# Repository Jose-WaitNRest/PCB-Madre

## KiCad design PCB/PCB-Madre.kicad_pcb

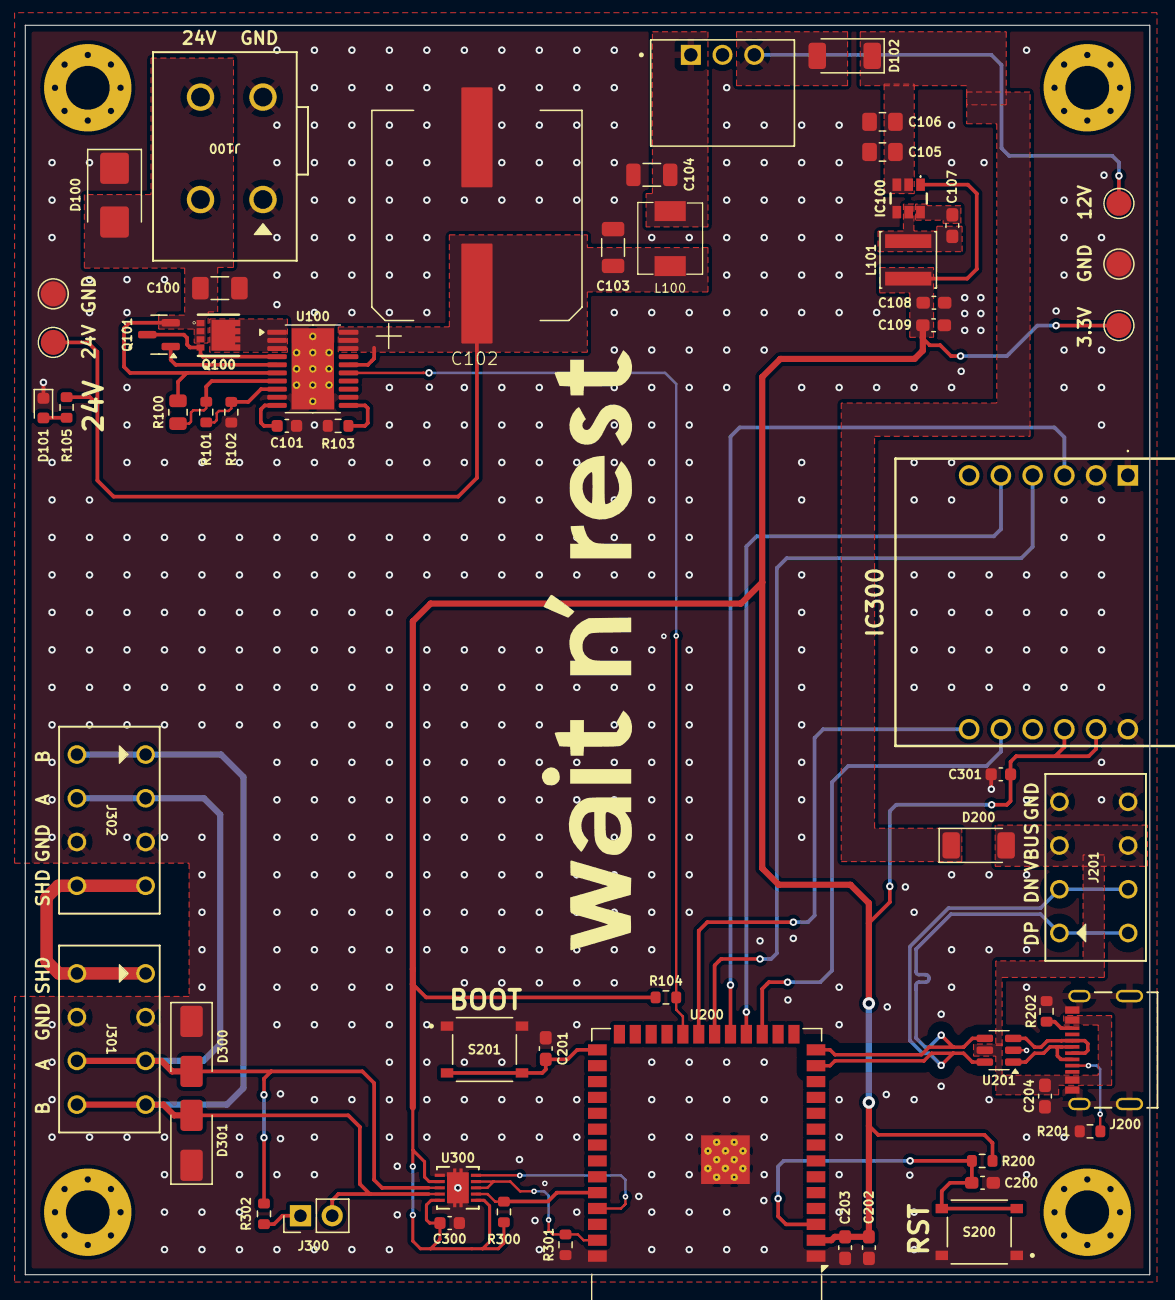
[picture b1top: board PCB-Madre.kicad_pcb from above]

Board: 4 copper layers, 90.0 x 100.0 mm, 63 parts (0 on the bottom side), 39 nets.

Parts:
C100: 1uF; C_1206_3216Metric_Pad1.33x1.80mm_HandSolder
C101, C300, C301: 0.1uF; C_0603_1608Metric
C102: 1mF/50V; VKMI1701H102MV
C103, C104: 22uF; C_1206_3216Metric
C105, C106: 10uF; C_0805_2012Metric_Pad1.18x1.45mm_HandSolder
C107, C200, C201, C203, C204: 0.1uF; C_0603_1608Metric_Pad1.08x0.95mm_HandSolder
C108, C109, C202: 22uF; C_0603_1608Metric_Pad1.08x0.95mm_HandSolder
D100: SMBJ28CA-13-F; D_SMB
D101: 19-21/GHC-YR1S2/4T; LED_0603_1608Metric
D102, D200: PMEG3030EP,115; D_SOD-128
D300, D301: SMAJ30CA; D_SMA
H1, H2, H3, H4: MountingHole_Pad; MountingHole_3.5mm_Pad_Via
IC100: AP63203WU-7; AP63203WU7
IC300: WIZ850IO
J100: 2604-3102
J200: 2171790001; MOLEX_2171790001
J201, J301, J302: 2086-1104; 2086-1104-THT
J300: jumper; PinHeader_1x02_P2.54mm_Vertical
L100: 4.7uH; MDA5030-4R7M
L101: 3.9uH; L_Sunlord_SWPA4030S
PS100: R-78K12-2.0; R-78K12-2_0
Q100: CSD19537Q3
Q101: BSS138; SOT-23
R100: 825K; R_0805_2012Metric
R101: 31.6K; R_0603_1608Metric
R102: 34K; R_0603_1608Metric
R103: 9.1K; R_0603_1608Metric
R104, R200, R300, R301: 10K; R_0603_1608Metric
R105: 2.2K; R_0603_1608Metric
R201, R202: 5.1K; R_0603_1608Metric
R302: 120; R_0603_1608Metric
S200, S201: TS-1187A-B-A-B
TP100, TP101, TP102, TP103, TP104: TestPoint; TestPoint_Pad_D2.0mm
U100: TPS26631PWP; HTSSOP-20-1EP_4.4x6.5mm_P0.65mm_EP3.4x6.5mm_Mask2.96x2.96mm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
U200: ESP32-S3-WROOM-1
U201: USBLC6-2SC6; SOT-23-6
U300: THVD2450VDRCR; VSON10_DRC_TEX

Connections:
+3.3V: C108.1, C109.1, C202.1, C203.1, C300.1, C301.1, IC100.1 (FB), IC300.J22 (3.3V_1), IC300.J23 (3.3V_2), L101.2, R104.1, R200.1, R300.1, TP103.1, U200.2 (3V3), U300.1 (VIO), U300.7 (SLR), U300.10 (VCC)
+12V: D102.2 (A), PS100.3 (+VOUT), TP102.1
+24V: C102.1, C103.1, L100.1, R105.1, TP100.1, U100.16 (PGTH), U100.18 (OUT), U100.19 (OUT), U100.20 (OUT)
/12V_5V: C105.1, C106.1, D102.1 (K), D200.1 (K), IC100.2 (EN), IC100.3 (VIN)
/MCU/BOOT: C201.1, S201.C, S201.D, U200.27 (IO0)
/MCU/CLK: IC300.J14 (SCLK), U200.20 (IO12)
/MCU/CS: IC300.J15 (SCNN), U200.18 (IO10)
/MCU/EN: C200.1, R200.2, S200.C, S200.D, U200.3 (EN)
/MCU/FLT: R104.2, U100.15 (~FLT), U200.22 (IO14)
/MCU/MISO: IC300.J26 (MISO), U200.21 (IO13)
/MCU/MOSI: IC300.J13 (MOSI), U200.19 (IO11)
/MCU/N: J200.A7 (DN1), J200.B7 (DN2), U201.1 (I/O1)
/MCU/P: J200.A6 (DP1), J200.B6 (DP2), U201.3 (I/O2)
/MCU/RS485_EN: R301.1, U200.39 (IO1), U300.3 (DE), U300.4 (*RE)
/MCU/RST: IC300.J25 (RSTN), U200.17 (IO9)
/MCU/RX: R300.2, U200.36 (RXD0), U300.2 (R)
/MCU/TX: U200.37 (TXD0), U300.5 (D)
/MCU/USB_N: J201.P2_1, J201.P2_2, U200.13 (IO19), U201.6 (I/O1)
/MCU/USB_P: J201.P1_1, J201.P1_2, U200.14 (IO20), U201.4 (I/O2)
/PERIPHERALS/A: D300.2 (A2), J301.P3_1, J301.P3_2, J302.P2_1, J302.P2_2, R302.2, U300.8 (A)
/PERIPHERALS/B: D301.2 (A2), J300.2, J301.P4_1, J301.P4_2, J302.P1_1, J302.P1_2, U300.9 (B)
/PERIPHERALS/SHIELD: J301.P1_1, J301.P1_2, J302.P4_1, J302.P4_2
/POWER/INPUT: C100.1, D100.2 (A2), J100.3 (2_1), J100.4 (2_2), Q100.1 (S), Q101.2 (S), R100.1, U100.6 (IN_SYS)
GND: C100.2, C101.1, C102.2, C103.2, C104.2, C105.2, C106.2, C108.2, C109.2, C200.2, C201.2, C202.2, C203.2, C204.2, C300.2, C301.2, D100.1 (A1), D101.1 (K), D300.1 (A1), D301.1 (A1), IC100.4 (GND), IC300.J11 (GND_1), IC300.J12 (GND_2), IC300.J21 (GND_3), J100.1 (1_1), J100.2 (1_2), J200.A1B12 (GND1), J200.B1A12 (GND2), J200.SH1 (SHIELD1), J200.SH2 (SHIELD2), J200.SH3 (SHIELD3), J200.SH4 (SHIELD4), J201.P4_1, J201.P4_2, J301.P2_1, J301.P2_2, J302.P3_1, J302.P3_2, PS100.2 (GND), R102.2, R103.2, R201.2, R202.2, R301.2, S200.A, S200.B, S201.A, S201.B, TP101.1, TP104.1, U100.9 (GND), U100.12 (MODE), U100.21 (GND), U200.1 (GND), U200.40 (GND), U200.41 (GND), U201.2 (GND), U300.6 (GND), U300.11 (GND)
unnamed: D101.2 (A), R105.2
unnamed: C107.2, IC100.6 (BST)
unnamed: C107.1, IC100.5 (SW), L101.1
unnamed: J200.A5 (CC1), R201.1
unnamed: J200.B5 (CC2), R202.1
unnamed: J300.1, R302.1
unnamed: C104.1, L100.2, PS100.1 (+VIN)
unnamed: Q100.3 (D), U100.1 (IN), U100.2 (IN), U100.3 (IN)
unnamed: Q100.2 (G), Q101.3 (D), U100.4 (B_GATE)
unnamed: Q101.1 (G), U100.5 (DRV)
unnamed: R103.1, U100.11 (ILIM)
unnamed: R101.2, R102.1, U100.8 (OVP)
unnamed: R100.2, R101.1, U100.7 (UVLO)
unnamed: C101.2, U100.10 (dVdT)
VBUS: C204.1, D200.2 (A), J200.A4B9 (VBUS1), J200.B4A9 (VBUS2), J201.P3_1, J201.P3_2, U201.5 (VBUS)

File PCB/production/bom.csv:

Designator,Footprint,Quantity,Value,LCSC Part #
C100,1206,1,1uF,C1848
"C101, C107, C200, C201, C203, C204, C300, C301",0603,8,0.1uF,C14663
C102,VKMI1701H102MV,1,1mF/50V,C487374
"C103, C104",1206,2,22uF,C342620
"C105, C106",0805,2,10uF,C440198
"C108, C109, C202",0603,3,22uF,C86295
D100,D_SMB,1,SMBJ28CA-13-F,C135064
D101,0603,1,19-21/GHC-YR1S2/4T,C2986048
"D102, D200",D_SOD-128,2,"PMEG3030EP,115",C255587
"D300, D301",D_SMA,2,SMAJ30CA,C83322
IC100,AP63203WU7,1,AP63203WU-7,C780769
IC300,WIZ850IO,1,WIZ850IO,
J100,2604-3102,1,2604-3102,
J200,MOLEX_2171790001,1,2171790001,C3197684
"J201, J301, J302",2086-1104-THT,3,2086-1104,
J300,PinHeader_1x02_P2.54mm_Vertical,1,jumper,C492401
L100,MDA5030-4R7M,1,4.7uH,C2847477
L101,L_Sunlord_SWPA4030S,1,3.9uH,C96899
PS100,R-78K12-2_0,1,R-78K12-2.0,
Q100,CSD19537Q3,1,CSD19537Q3,C478469
Q101,SOT-23,1,BSS138,C40912
R100,0805,1,825K,C49010125
R101,0603,1,31.6K,C25967
R102,0603,1,34K,C23008
R103,0603,1,9.1K,C23260
"R104, R200, R300, R301",0603,4,10K,C25804
R105,0603,1,2.2K,C4190
"R201, R202",0603,2,5.1K,C23186
R302,0603,1,120,C22787
"S200, S201",TS-1187A-B-A-B,2,TS-1187A-B-A-B,C318884
"TP100, TP101, TP102, TP103, TP104",TestPoint_Pad_D2.0mm,5,TestPoint,
U100,HTSSOP-20-1EP_4.4x6.5mm_P0.65mm_EP3.4x6.5mm_Mask2.96x2.96mm_ThermalVias,1,TPS26631PWP,C2832195
U200,ESP32-S3-WROOM-1,1,ESP32-S3-WROOM-1,C2913202
U201,SOT-23-6,1,USBLC6-2SC6,
U300,VSON10_DRC_TEX,1,THVD2450VDRCR,C5960705

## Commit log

2026-03-17 Creacion de la estructura
    Se creo:
    - Estructura de los folders
    - Creación del archivo KICAD
    - 80% del esquematico
2026-03-18 pcb board terminada
    Se termino:
    - PCB board
    - Labels de conectores y logo de la empresa
    - Conexion WIZ850IO
    - Conexion de MCU y WIZ850IO
2026-04-05 Mejora de ruteo
    - Se ha mejorado el ruteo del sector de potencia
2026-04-06 Cambio del footprint Efuse
    - Se ha cambiado el footorint de chip Efuse debido a que el utilizado no habia stock en JLCPCB
    - Se ha creado los archivos de configuracion para JLCPCB
2026-04-07 Fix Stitching vias y USB trace clearance
    * Se eliminaron las vías que se encontraban demasiado cercanas a componentes o a ciertas zonas, lo cual representaba un problema común generado por el uso de *stitching vias*.
    * Se definió un *clearance* de 0.8 mm para las pistas USB, con el fin de respetar el cálculo de impedancia bajo una configuración *no coplanar*. Esto se debe a que, al estar la PCB completamente rode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
